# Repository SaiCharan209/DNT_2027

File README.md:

# DNT_2027
Data &amp; Telemetry Printed Circuit Board for the Team Averera

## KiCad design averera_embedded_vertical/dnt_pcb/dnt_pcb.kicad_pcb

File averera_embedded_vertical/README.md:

This is the official GitHub repository of Team AVERERA Embedded Team

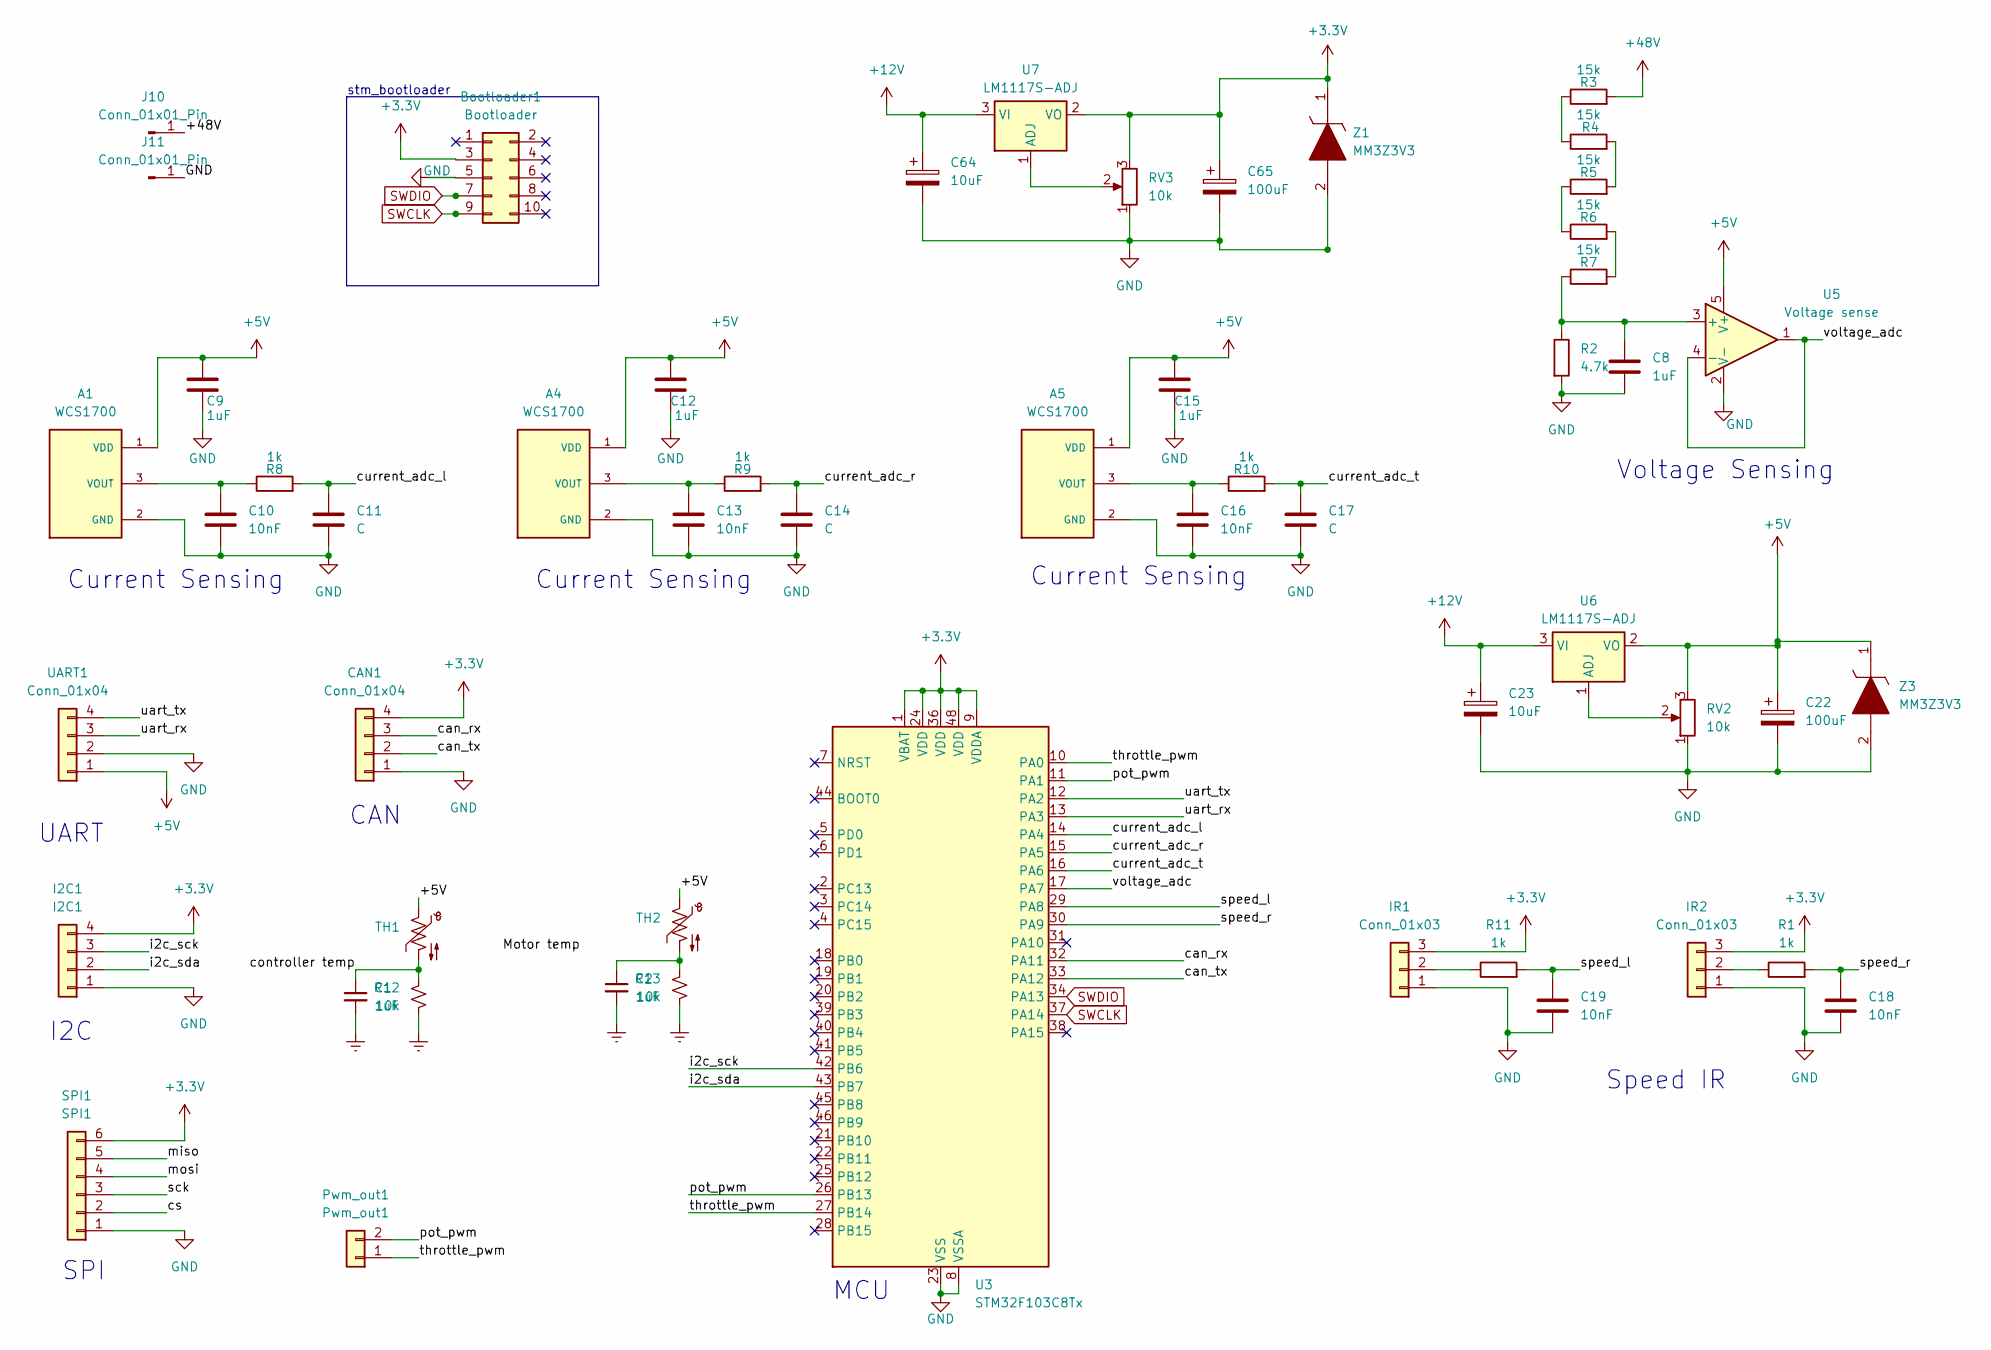
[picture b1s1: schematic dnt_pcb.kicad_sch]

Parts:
A1, A4, A5: WCS1700; WCS1600; PARTREV 2024/7/30
Bootloader1: Bootloader; PinHeader_2x05_P2.54mm_Vertical
C1, C2: 1uF; C_0805_2012Metric_Pad1.18x1.45mm_HandSolder
C8, C9, C12, C15: 1uF; C_0201_0603Metric_Pad0.64x0.40mm_HandSolder
C10, C13, C16, C18, C19: 10nF; C_0201_0603Metric_Pad0.64x0.40mm_HandSolder
C11, C14, C17: C; C_0201_0603Metric_Pad0.64x0.40mm_HandSolder
C22, C65: 100uF; C_Elec_6.3x7.7
C23, C64: 10uF; CP_Radial_D5.0mm_P2.50mm
CAN1: Conn_01x04; PinHeader_1x04_P2.54mm_Vertical
I2C1: I2C1; PinHeader_1x04_P2.54mm_Vertical
IR1, IR2: Conn_01x03; PinHeader_1x03_P2.54mm_Vertical
J10, J11: Conn_01x01_Pin; Banana_Jack_1Pin
Pwm_out1: Pwm_out1; PinHeader_1x02_P2.54mm_Vertical
R1, R8, R9, R10, R11: 1k; R_0402_1005Metric_Pad0.72x0.64mm_HandSolder
R2: 4.7k; R_Axial_DIN0309_L9.0mm_D3.2mm_P12.70mm_Horizontal
R3, R4, R5, R6, R7: 15k; R_1206_3216Metric_Pad1.30x1.75mm_HandSolder
R12, R13: 10k; R_0805_2012Metric
RV2, RV3: 10k; Potentiometer_Runtron_RM-065_Vertical
SPI1: SPI1; PinHeader_1x06_P2.54mm_Vertical
TH1: Thermistor_NTC_US; R_Radial_Power_L7.0mm_W8.0mm_Px2.40mm_Py2.30mm
TH2: Thermistor_NTC_US; Thermistor
U3: STM32F103C8Tx; LQFP-48_7x7mm_P0.5mm
U5: Voltage sense; SOT-23-5_HandSoldering
U6, U7: LM1117S-ADJ; 1117s_ADJ
UART1: Conn_01x04; PinHeader_1x04_P2.54mm_Vertical
Z1, Z3: MM3Z3V3; D_SOD-323_HandSoldering; Manufacturer_Part_Number 1N4728A; Mouser Part Number 512-1N4728A

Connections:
+3.3V: Bootloader1.3, C65.1, CAN1.4, I2C1.4, IR1.3, IR2.3, RV3.3, SPI1.6, U3.1 (VBAT), U3.9 (VDDA), U3.24 (VDD), U3.36 (VDD), U3.48 (VDD), U7.2 (VO), Z1.1; also elsewhere on the board
+5V: A1.1 (VDD), A4.1 (VDD), A5.1 (VDD), C9.1, C12.1, C15.1, C22.1, RV2.3, TH1.1, TH2.1, U5.5 (V+), U6.2 (VO), UART1.1, Z3.1; also elsewhere on the board
+12V: C23.1, C64.1, U6.3 (VI), U7.3 (VI); also elsewhere on the board
+48V: J10.1, R3.2
/can_rx: CAN1.3, U3.32 (PA11)
/can_tx: CAN1.2, U3.33 (PA12)
/controller temp: C1.1, R12.2, TH1.2
/cs: SPI1.2
/current_adc_l: C11.1, R8.2, U3.14 (PA4)
/current_adc_r: C14.1, R9.2, U3.15 (PA5)
/current_adc_t: C17.1, R10.2, U3.16 (PA6)
/i2c_sck: I2C1.3, U3.42 (PB6)
/i2c_sda: I2C1.2, U3.43 (PB7)
/miso: SPI1.5
/mosi: SPI1.4
/pot_pwm: Pwm_out1.2, U3.11 (PA1), U3.26 (PB13)
/sck: SPI1.3
/speed_l: C19.1, R11.2, U3.29 (PA8)
/speed_r: C18.1, R1.2, U3.30 (PA9)
/throttle_pwm: Pwm_out1.1, U3.10 (PA0), U3.27 (PB14)
/uart_rx: U3.13 (PA3), UART1.3
/uart_tx: U3.12 (PA2), UART1.4
/voltage_adc: U3.17 (PA7), U5.1, U5.4 (-)
GND: A1.2 (GND), A4.2 (GND), A5.2 (GND), Bootloader1.5, C8.2, C9.2, C10.2, C11.2, C12.2, C13.2, C14.2, C15.2, C16.2, C17.2, C18.2, C19.2, C22.2, C23.2, C64.2, C65.2, CAN1.1, I2C1.1, IR1.1, IR2.1, J11.1, R2.2, RV2.1, RV3.1, SPI1.1, U3.8 (VSSA), U3.23 (VSS), U3.35 (VSS), U3.47 (VSS), U5.2 (V-), UART1.2, Z1.2, Z3.2; also elsewhere on the board
GNDREF: C1.2, C2.2, R12.1, R13.1
unnamed: A1.3 (VOUT), C10.1, R8.1
unnamed: A4.3 (VOUT), C13.1, R9.1
unnamed: A5.3 (VOUT), C16.1, R10.1
unnamed: C2.1, R13.2, TH2.2
unnamed: IR1.2, R11.1
unnamed: IR2.2, R1.1
unnamed: R3.1, R4.1
unnamed: R4.2, R5.2
unnamed: R5.1, R6.1
unnamed: R6.2, R7.2
unnamed: C8.1, R2.1, R7.1, U5.3 (+)
unnamed: RV2.2, U6.1 (ADJ)
unnamed: RV3.2, U7.1 (ADJ)
SWCLK: Bootloader1.9, U3.37 (PA14)
SWDIO: Bootloader1.7, U3.34 (PA13)

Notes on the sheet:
Voltage Sensing
I2C
stm_bootloader
CAN
UART
MCU
Speed IR
Current Sensing
SPI

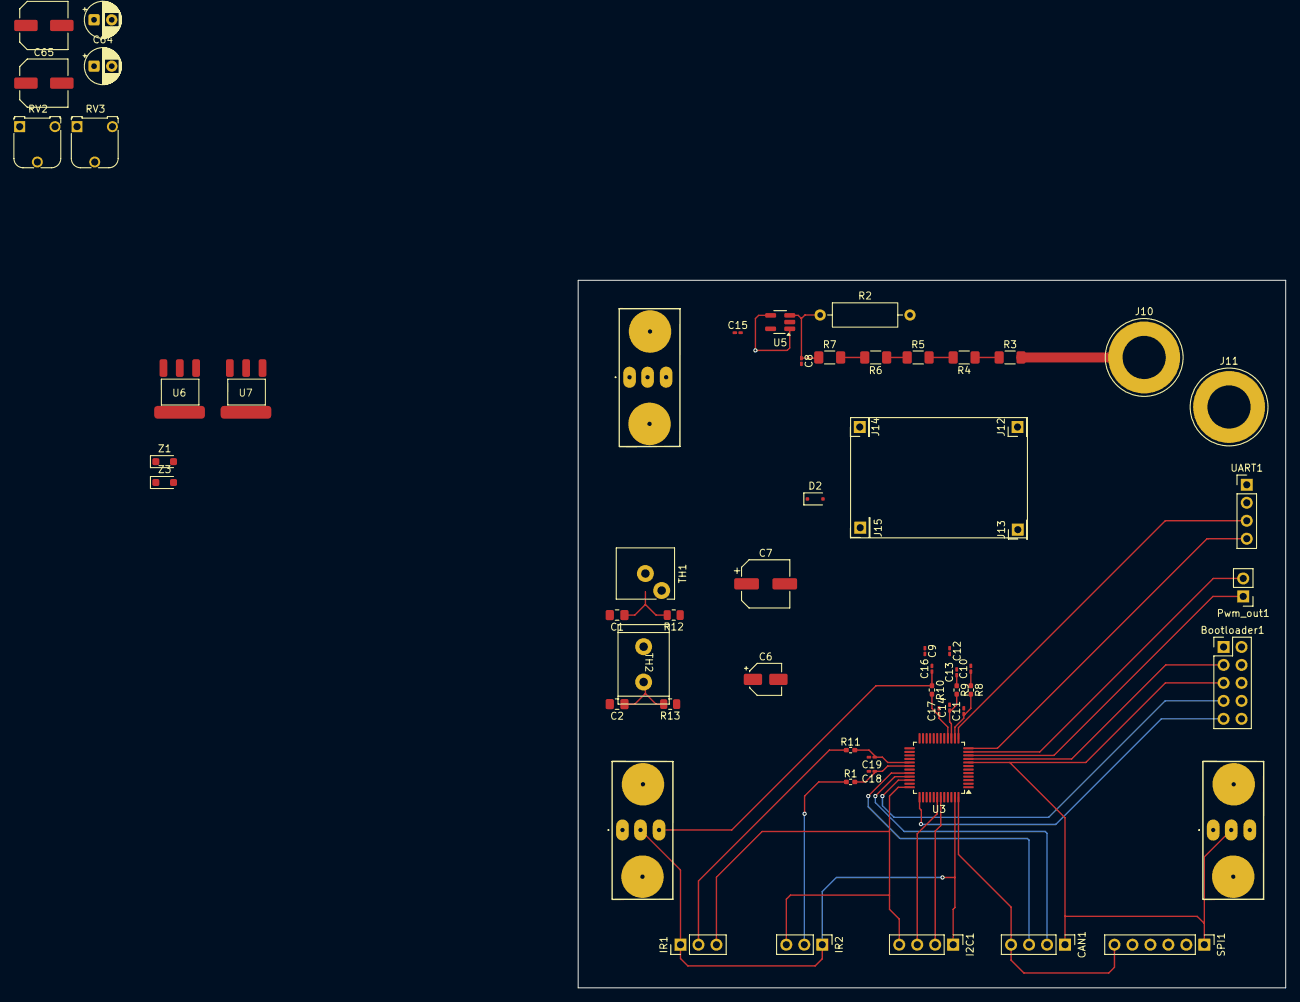
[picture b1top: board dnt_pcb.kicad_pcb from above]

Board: 2 copper layers, 100.0 x 100.0 mm, 61 parts (0 on the bottom side), 36 nets.

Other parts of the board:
C6: 10uF; CP_Elec_4x5.7
C7: 100uF; CP_Elec_6.3x7.7
D2: MM3Zxx; D_SOD-323F
J12, J13, J14, J15: Conn_01x01_Pin; PinHeader_1x01_P2.54mm_Vertical

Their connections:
+3.3V: C7.1, D2.1 (K); also elsewhere on the board
+5V: C6.1; also elsewhere on the board
+12V: J14.1; also elsewhere on the board
GND: C6.2, C7.2, D2.2 (A), J13.1, J15.1; also elsewhere on the board

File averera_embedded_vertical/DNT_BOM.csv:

"Reference","Value","Datasheet","Footprint","Qty","DNP"
"A1,A4,A5","WCS1700","","Project:WCS1600","3",""
"C1,C2","1uF","~","Capacitor_SMD:C_0805_2012Metric_Pad1.18x1.45mm_HandSolder","2",""
"C6","10uF","~","Capacitor_SMD:CP_Elec_4x5.7","1",""
"C7","100uF","~","Capacitor_SMD:CP_Elec_6.3x7.7","1",""
"C8,C9,C12,C15","1uF","~","Capacitor_SMD:C_0201_0603Metric_Pad0.64x0.40mm_HandSolder","4",""
"C10,C13,C16,C18,C19","10nF","~","Capacitor_SMD:C_0201_0603Metric_Pad0.64x0.40mm_HandSolder","5",""
"C11,C14,C17","C","~","Capacitor_SMD:C_0201_0603Metric_Pad0.64x0.40mm_HandSolder","3",""
"CAN1,I2C1,UART1","Conn_01x04","~","Connector_PinHeader_2.54mm:PinHeader_1x04_P2.54mm_Vertical","3",""
"D2","MM3Zxx","https://diotec.com/tl_files/diotec/files/pdf/datasheets/mm3z2v4.pdf","Diode_SMD:D_SOD-323F","1",""
"IR1,IR2","Conn_01x03","~","Connector_PinHeader_2.54mm:PinHeader_1x03_P2.54mm_Vertical","2",""
"J8","Conn_02x05_Odd_Even","~","Connector_PinHeader_2.54mm:PinHeader_2x05_P2.54mm_Vertical","1",""
"J10,J11","Conn_01x01_Pin","~","Connector:Banana_Jack_1Pin","2",""
"Pwm_out1","Conn_01x02","~","Connector_PinSocket_2.54mm:PinSocket_1x02_P2.54mm_Vertical","1",""
"R1,R8,R9,R10,R11","1k","~","Resistor_SMD:R_0402_1005Metric_Pad0.72x0.64mm_HandSolder","5",""
"R2","4.7k","~","Resistor_THT:R_Axial_DIN0309_L9.0mm_D3.2mm_P12.70mm_Horizontal","1",""
"R3,R4,R5,R6,R7","15k","~","Resistor_SMD:R_1206_3216Metric_Pad1.30x1.75mm_HandSolder","5",""
"R12,R13","10k","~","Resistor_SMD:R_0805_2012Metric","2",""
"SPI1","Conn_01x06","~","Connector_PinHeader_2.54mm:PinHeader_1x06_P2.54mm_Vertical","1",""
"TH1,TH2","Thermistor_NTC_US","~","Project:Thermistor","2",""
"U2","LM1117S-3.3","http://www.ti.com/lit/ds/symlink/lm1117.pdf","LM1117s-ADJ:1117s_ADJ","1",""
"U3","STM32F103C8Tx","https://www.st.com/resource/en/datasheet/stm32f103c8.pdf","Package_QFP:LQFP-48_7x7mm_P0.5mm","1",""
"U5","MCP6001-OT","https://ww1.microchip.com/downloads/en/DeviceDoc/MCP6001-1R-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","Package_TO_SOT_SMD:SOT-23-5_HandSoldering","1",""
